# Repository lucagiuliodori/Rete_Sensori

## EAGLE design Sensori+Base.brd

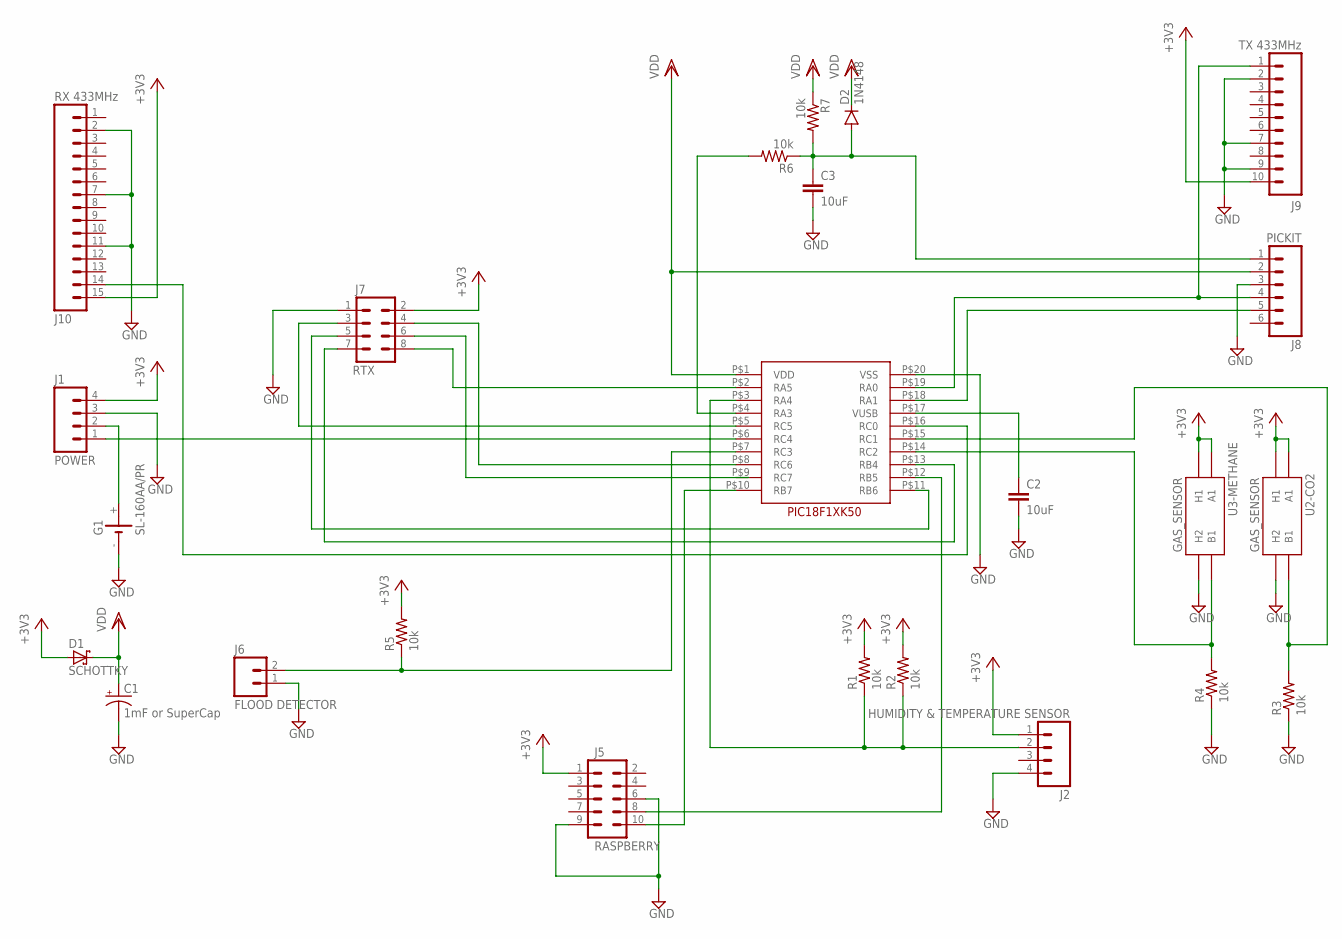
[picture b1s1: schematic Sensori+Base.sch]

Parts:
C1: 1mF or SuperCap; CPOL-RADIAL-1000UF-25V
C2, C3: 10uF; 0603-CAP
D1: SCHOTTKY; F126Z12
D2: 1N4148; DIODE-1N4148
G1: SL-160AA/PR
J1: POWER; 1X04_NO_SILK_ALL_ROUND
J2: HUMIDITY & TEMPERATURE SENSOR; 1X04_NO_SILK_ALL_ROUND
J5: RASPBERRY; 2X5_NOSILK
J6: FLOOD DETECTOR; 1X02_NO_SILK
J7: RTX; 2X4
J8: PICKIT; 1X06_NO_SILK
J9: TX 433MHz; 1X10_NO_SILK
J10: RX 433MHz; 1X15
R1, R2, R3, R4, R5, R6, R7: 10k; AXIAL-0.3EZ
U2-CO2, U3-METHANE: GAS_SENSOR; MQ-3
U$1: PIC18F1XK50; SPDIP-20PIN

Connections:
+3V3: D1.A, J1.4, J2.1, J5.1, J7.2, J9.10, J10.15, R1.P$2 (2), R2.P$2 (2), R5.P$2 (2), U2-CO2.A1, U2-CO2.HA (H1), U3-METHANE.A1, U3-METHANE.HA (H1)
GND: C1.2 (-), C2.2, C3.2, G1.-, J1.3, J2.4, J5.6, J5.9, J6.1, J7.1, J8.3, J9.2, J9.7, J9.9, J10.2, J10.7, J10.11, R3.P$1 (1), R4.P$1 (1), U2-CO2.HB (H2), U3-METHANE.HB (H2), U$1.P$20 (VSS)
unnamed: J7.3, U$1.P$5 (RC5)
unnamed: J7.4, U$1.P$8 (RC6)
unnamed: J7.5, U$1.P$11 (RB6)
unnamed: J7.7, U$1.P$13 (RB4)
unnamed: J7.8, U$1.P$2 (RA5)
unnamed: J1.1, U$1.P$6 (RC4)
unnamed: G1.+, J1.2
unnamed: J2.2, R1.P$1 (1), R2.P$1 (1), U$1.P$3 (RA4)
unnamed: R4.P$2 (2), U3-METHANE.B1, U$1.P$14 (RC2)
unnamed: R3.P$2 (2), U2-CO2.B1, U$1.P$15 (RC1)
unnamed: J5.10, U$1.P$10 (RB7)
unnamed: J5.8, U$1.P$12 (RB5)
unnamed: J6.2, R5.P$1 (1), U$1.P$7 (RC3)
unnamed: R6.P$2 (2), U$1.P$4 (RA3)
unnamed: J8.4, J9.1, U$1.P$19 (RA0)
unnamed: J8.5, U$1.P$18 (RA1)
unnamed: C2.1, U$1.P$17 (VUSB)
unnamed: C3.1, D2.A, J8.1, R6.P$1 (1), R7.P$2 (2)
unnamed: J10.14, U$1.P$16 (RC0)
VDD: C1.1 (+), D1.C, D2.C, J8.2, R7.P$1 (1), U$1.P$1 (VDD)

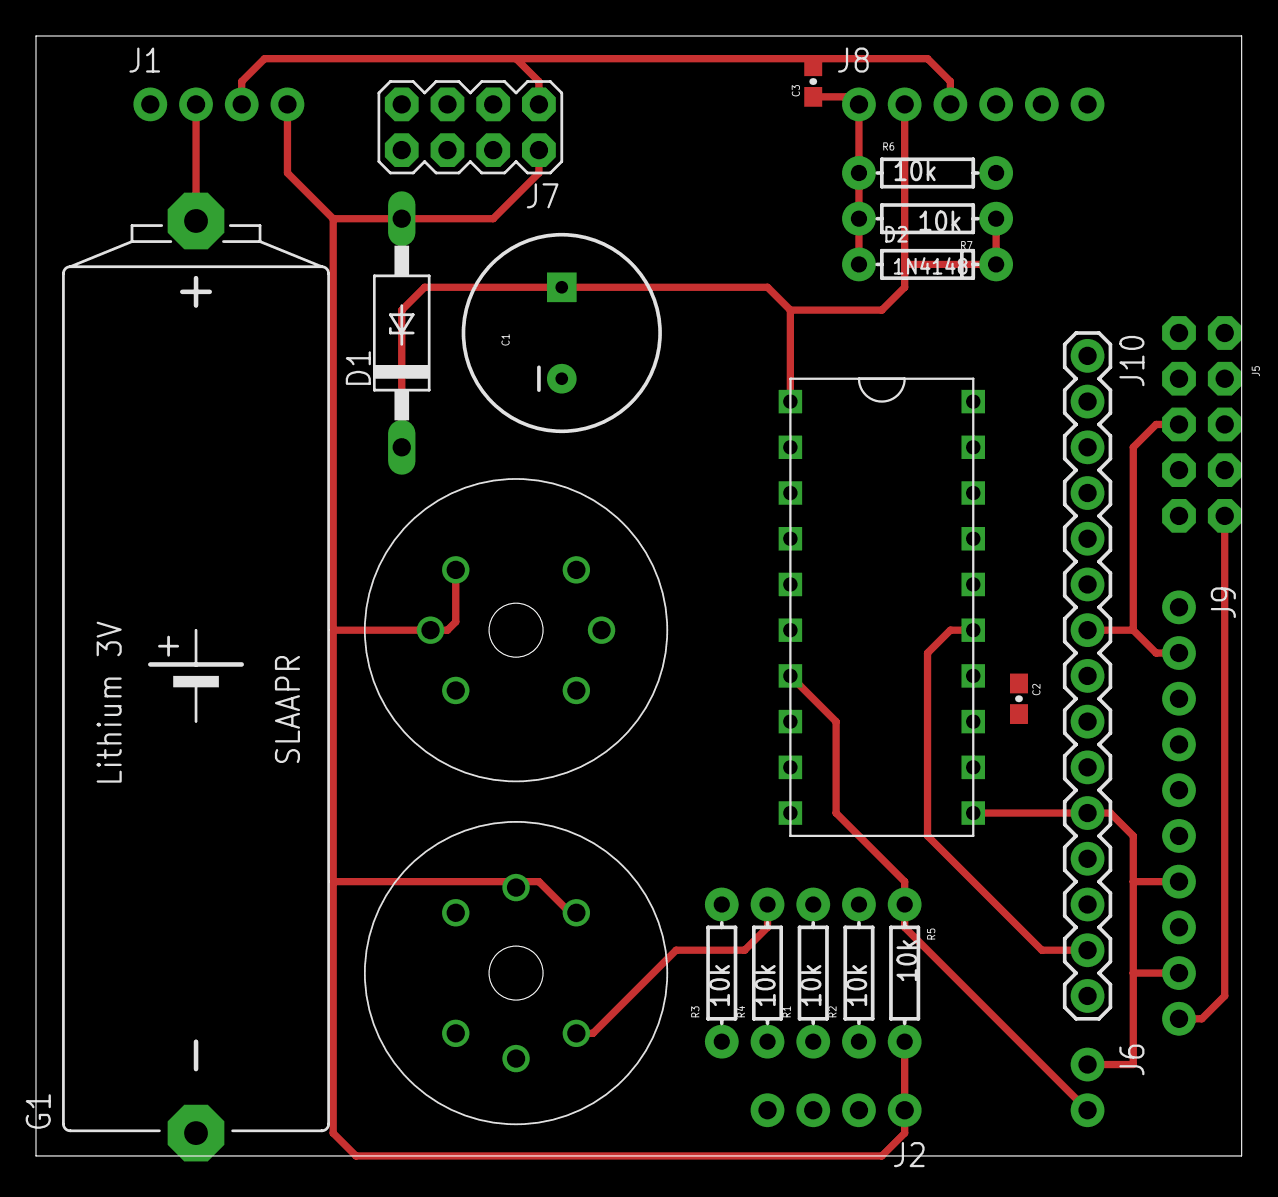
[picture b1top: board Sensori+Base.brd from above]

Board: 2 copper layers, 67.0 x 62.2 mm, 24 parts (0 on the bottom side), 22 nets.

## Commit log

2017-08-17 Initial adding files
2017-08-18 Change paths

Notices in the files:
parts and their libraries:
SparkFun-Passives: Licensing: Creative Commons ShareAlike 4.0 International - https://creativecommons.org/licenses/by-sa/4.0
